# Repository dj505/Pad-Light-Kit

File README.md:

# Overkill PIU Pad Lighting Kit
An upgrade kit, if you consider a 5x5 RGB LED grid in the center of each panel to be an upgrade.  

# What is this?
I wanted to make a drop-in kit that replaced the original LEDs in Pump it Up dance pads with fancy StepManiaX-like RGB lighting. **This is only partially that.** Due to a variety of factors, it's not quite as drop-in as I'd hoped, but installation is still rather straightforward!

There are 2 PCB designs being worked on for this project:
* The main "Panel" PCB
    * Contains all the LEDs, with individual microcontrollers per PCB, ensuring they can all work individually.
    * Fully tested, with updated design/gerber files that hardware issues I initially ran into while prototyping.
* The power distrubution PCB
    * Takes a barrel jack and/or bare wires via screw terminals.
    * 5V input only! Make sure your power supply can pump out enough amps to power all the LEDs.
    * 5 outputs, one per arrow on one pad. In the case of DDR/ITG pads, one may be left unused.
    * Also includes footprints for filtering capacitors, which I haven't found to be necessary. Populate with 10uF 0805 capacitors if needed.

Unlike the PicoFX and my other previous hardware projects, this kit is not meant to be hand-soldered, although hand-solder friendly footprints were used where possible. As this likely will not be sold as a pre-made kit any time soon, be aware that it is not a beginner project. PCB manufacturing and assembly costs are rather affordable, but costs from part sourcing and shipping could add up.

# Compatibility & Overview

### This project is designed to be as easy as possible to install, but does require you to do some amount of manual part sourcing. Please pay close attention to power consumption and make sure you source parts that can support the kit.

This project is made for somewhat modern Pump it Up dance pads (FX through LX), but is plug-and-play compatible with:
* All Pump it Up dance pads **after** SD (SD pads used incandescent bulbs and will require some modification for use with this kit)
* In the Groove pads
* Older Dance Dance Revolution pads that use the same 2.54mm pitch connector (double check first!)
Please **pay close attention to the polarity** of the 12V connector printed on the PCB's silkscreen.  
The **yellow wire should go to 12V.** This may involve plugging the cable in upside down. That's okay. Just keep in mind the pins may need to be bent upwards slightly to accept the connector.

Without some modification to the pads and/or this kit, this project is untested or **NOT** plug-and-play compatible with:
* Pump it Up JUMP pads (unfortunate, I know)
* Modern Dance Dance Revolution pads
* Namco "Crapocab" DDR pads
* StepManiaX pads (for several reasons)
* Dance Master Super Station/3DDX
* EZ2Dancer
If the pads you want to use this project with have a **12V DC** wire that powers the original lights, whether it goes to existing LEDs or to an inverter, **this kit will function, but may require you to cut the wires and/or splice in a new connector.** It likely will also not fit the original mounting holes, in which case you'll need to tape it down or something.

Aside from the individual components required for each PCB, you will need:
* As many "Panel" PCBs as your upgrade requires
    * PIU pads require 5 per full pad, 10 in total for a complete setup
    * ITG/DDR pads require 4 per full pad, 8 in total for a complete setup
* A way to supply 5V with up to ~10A maximum current draw (50W or so)
    * This can be either one 5A power supply **per pad**, or one single super beefy power supply for **both pads simultaneously.**
    * If I did my math right, these metrics are based on the peak power comsumption when every single LED is lit up white at full brightness. **Only run your LEDs on full-brightness white for extended periods of time at your own risk; the kit was not developed with this use in mind.** (It would be bright as heck, though)
* Extra wiring to supply power to the new PCBs
    * I recommend 20AWG, anything thinner is not rated for the possible peak power consumption of one panel
* 2 pin male JST connectors (along with metal connector to be crimped to the wires)
    * These are listed here separately from the female connectors in the bill of materials, as you'll need quite a few.
    * 2 connectors are required per panel. One to connect to the lighting PCB, one to connect to the power distribution board.
* A crimping tool compatible with JST XH connectors (optional, but recommended)

# Main panel PCB
A full BOM can be generated using KiCad's schematic editor. Unlike my previous projects, such as the PicoFX or PicoIO, there are a *lot* of components that you will likely need to source yourself. Many of these have LCSC part numbers attached as an example, but are not guaranteed to be available through JLCPCB's assembly service.  
The following components (some of which are not required) are listed per **single** PCB:

### Bill of materials
|          Component          |              Reference              |          Footprint         |Quantity|
|-----------------------------|-------------------------------------|----------------------------|--------|
|100nF Capacitor              |C1, C2, C4, C5, C7-C9, C12, C14, C15 |SMD 0402                    |10      |
|1uF Capacitor                |C3, C6                               |SMD 0402                    |2       |
|27pF Capacitor               |C10, C11                             |SMD 0402                    |2       |
|10uF Capacitor               |C13, C16                             |SMD 0402                    |2       |
|WS2812B-V5 LED (!)           |D1-10, D12-26                        |PLCC4 5x5mm                 |25      |
|SS34 Diode                   |D27                                  |DO-214AC                    |1       |
|Green LED                    |D28                                  |SMD 0805                    |1       |
|nSMD025 Fuse                 |F1                                   |SMD 1206                    |1       |
|3 Pin Header \*              |J1                                   |2.54mm Pitch                |1       |
|USB Type C Port              |J2                                   |G-Switch GT-USB 7010ASV     |1       |
|2 Pin JST XH                 |J3                                   |2.50mm Pitch                |1       |
|2x6 Pin Header \*            |J4                                   |2.54mm Pitch                |1       |
|Molex 35312-0760 \~\~        |J5                                   |N/A                         |1       |
|Molex Mini-Fit Jr \~\~       |J6-J9                                |N/A                         |4       |
|2 Pin Header \~              |J10                                  |2.54mm Pitch, **Horizontal**|1       |
|3 Pin Header \*\*            |J11, J12                             |1.27mm Pitch, Not Required  |2       |
|1k Ohm Reistor               |R1, R8, R10                          |SMD 0402                    |3       |
|10k Ohm Resistor             |R2                                   |SMD 0402                    |1       |
|10K Ohm Resistor \*\*        |R3                                   |SMD 0402 (for SPI flash)    |1       |
|27 Ohm Resistor              |R4, R5                               |SMD 0402                    |2       |
|5.1k Ohm Resistor            |R6, R7                               |SMD 0402                    |2       |
|3k Ohm Resistor              |R9                                   |SMD 0402                    |1       |
|Tactile Button Switch        |SW1, SW2                             |6mm x 6mm                   |2       |
|W25Q32JVSS (or equivalent)   |U1                                   |SOIC-8                      |1       |
|Raspberry Pi RP2040          |U2                                   |QFN-56                      |1       |
|NCP1117 3.3V Output Regulator|U3                                   |SOT-223-3                   |1       |
|12.000MHz Crystal Oscillator |Y1                                   |HC49                        |1       |

(!) WS2812B-V5 LEDs don't require external capacitors, so there are no footprints for them on this board. Earlier revisions may not work properly without these capacitors.
\* Optional  
\*\* Do Not Fit (only required if a part malfunctions without it)  
\~ Required for old-style pads (FX and earlier)  
\~\~ Required for new-style pads (CX/TX and newer)  

All **SMD 0402** parts use hand-solder footprints in just in case, however if you do not own a reflow oven or hot air soldering station, please consider using an assembly service available through companies like PCBWay or JLCPCB for a better and more realiable end result. It does cost extra, but will be far less time consuming and far more reliable than soldering hundreds of components by hand.

# Power PCB
This part is extremely basic and just supplies power to the panels. Each PCB should be capable of supplying up to 8A, enough to power all 5 panels. Just make sure to hook it up to a power supply capable of delivering the necessary wattage.

### Bill of materials
|          Component          | Reference |          Footprint         |Quantity|
|-----------------------------|-----------|----------------------------|--------|
|10uF Capacitor \*            |C1-C5      |SMD 0805                    |5       |
|2 Pin Screw Terminal \*\*    |J1         |5mm Plugin Terminal         |1       |
|DC Barrel Jack \*\*          |J2         |2.5mm inner, 6.4mm Outer    |1       |
|2 Pin JST XH                 |J3-J7      |2.50mm Pitch                |5       |

\* Option/not strictly necessary. Serves a purpose, but shouldn't affect functionality if missing.  
\*\* Denotes parts that are interchangeable depending on how you want to power the board

This board lacks mounting holes and is intended to just be attached somewhere near the foot PCB or power supply with double sided tape. Placement is up to you. Footprints for a screw terminal and a DC jack are provided, depending on which is more suited to your use case. You could even solder the power wires straight to the PCB if you really want to.  

JST XH connectors with 20AWG wire will need to be routed from the power distrubution PCB to every individual panel PCB. This shouldn't be all that difficult, just a little extra time consuming. Having a crimping tool would make this far easier.

# Very Important Notes
**(Seriously, you're going to want to double check these!)**

### This kit will require dedicated external power, and there's no safe way around that!
This kit bumps the LED count up to 125 per pad. Stock pads have around 40 or fewer depending on pad model. Please don't try to power this off the cab's original 12V line! The original 22AWG wire is rated for roughly 0.92A. This kit can potentially draw up to 1A per panel, or 5A total per pad. Plus, the 12V line is used for signalling purposes with this kit, and it won't function correctly without it. **I've measured a draw of 0.874A for a single panel lit up white at full brightness, however this may not be consistent from build to build.** While 10A total is a worst-case scenario, be sure to stick to the following guidelines:  
* Make sure you use a power supply that's capable of supplying the necessary amount of power required by this kit, and pick a wire gauge capable of carrying the amount of power needed for each panel. I would recommend 20AWG.  
* You'll need a way to run power into the pads. If I can come up with a more elegant solution I'll be sure to post it in detail, but the holes present in the bottom corners of each arrow are safe bets as entry points for your wires.
* Even if you don't plan on running these at high enough power to draw 5A per pad (or the maximum you have measured on your own), don't skimp out on a power supply. Overdrawing the power supply will cause it to get uncomfortably warm (or worse), and will eventually destroy it. Spend the extra few bucks for safety!

### Make sure you use a bright solder mask!
White is recommended, green and others may also work, but black solder mask isn't known to be very reflective. It won't make a very big difference, but it will definitely look better and brighter.

### If you own a multimeter, check the voltage of the 12V line!
These boards get their "turn on and start animating" signal from the original 12V wiring that's meant to power the stock LEDs/inverters/what have you. To make this safe for the 3.3V RP2040 chip, a voltage divider is used. Until this design is eventually replaced with an optoisolator or other component, **you should do the following:**  
1. Unplug the stock LED
2. Hook up a voltmeter or a multimeter in DC mode to the connector
3. Ensure the connector supples **no less than 10V** and **no more than 13.2V** when supplying power  
If your measurement falls outside of this range and the power supply in your cab isn't adjustable, you may need to use different reistors for the voltage divider circuit.

If the connector is not supplying enough power, the microcontroller won't read it as a "high" signal to start animating the lights. If it's *too* high, you risk damaging the microcontroller. I've haven't seen any machines deviate from this general range before, so chances are you're fine, but make sure to double check. If your machine has a variable voltage power supply **and you know what you're doing**, you can adjust it slightly to fit within the safe range.

# Firmware Setup
This project runs on [CircuitPython for the Raspberry Pi Pico.](https://circuitpython.org/board/raspberry_pi_pico/). I'm not quite clever enough to create a special CircuitPython build specifically for this project yet, maybe one day!

1. Download the .uf2 file for CircuitPython. This project was developed using 7.3.3, but in between writing the firmware and actually receiving all the parts for a kit, 8.0.0 was released as a stable version, so the following instructions have been updated.
2. Plug the board into your PC. The BOOTSEL button shouldn't need to be held as the board should not yet be programmed. If for some reason it already is, use the BOOTSEL button.
3. The board should pop up as a USB mass storage device. Drag and drop the .uf2 file onto it. After a moment, it should disconnect, and you should see a "CIRCUITPY" drive appear in its place.
4. Open the "CIRCUITPY" drive, and copy the contents of this repository's "Firmware" directory onto it, overwriting code.py.
5. Download the [CircuitPython library bundle](https://circuitpython.org/libraries) that matches the version of CircuitPython you installed.
    * Look inside the "lib" directory for an "asyncio" folder. Copy this to the CIRCUITPY drive's "lib" folder.
    * Do the same for "adafruit_pixelbuf.mpy", "adafruit_ticks.mpy", and "neopixel.mpy".
6. Create your animations. See the instructions in /Firmware/README.md or use the included example animations.
    * Your animation should be a bitmap file titled "image.bmp" and located in the "bitmap" directory.
    * By default, there won't be a "bitmap" directory. You'll need to create this by hand or copy over the example one.
7. You're done! If everything is assembled and set up properly, your animations should now work, and the panel is ready to be installed.

# Installation
After assembling and setting up the firmware for each of the panels, actually installing them is the easy part. I'll update this section with photos when I have some.

1. Unplug and remove the original LEDs, and replace them with the new boards.
    * If the mounting holes *do* line up, use the original screws to secure the new boards in place.
    * If the mounting holes *don't* line up, double sided tape will do the trick!
    * You may have to remove some original parts to make room, depending on the pad. This mostly applies to much older pads that have fluorescent lights hooked up to inverters. Carefully remove these (they may be fragile!) and set them aside.
2. Find a power supply, and plan out where the wires are going to go.
    * I find the easiest way to do this is to hide the power supply underneath the dance pad and run the cable coming from the low voltage side in through the one of the 4 holes in the bottom of one of the arrow panels.
    * I would not recommend routing any AC wiring or power supply units inside of the dance pads for safety reasons. It's much safer to run the low voltage DC side in alone.
3. Mount the power distribution PCB.
    * Make sure it's within easy reach of the cable you'll be using to power it.
    * The placement here is entirely up to your discretion, just put it somewhere that allows you to easily run all the necessary wires. I mounted mine under the center panel.
    * This PCB has no mounting holes, since you'll be using double sided tape or other similar adhesive to mount it. Make sure any exposed contacts on the bottom are trimmed down and/or covered and so they do not make contact with the pad frame.
4. Run wires from the distribution board's outputs to each of your panels.
    * If you know what you're doing, and you thoroughly test the power consumption of your components, be sure to use a wire rated for the power draw. Otherwise, I recommend 20AWG wire. I personally measured a 0.874A peak power draw, but your build may differ.
    * You can either try to source wires with JST XH connectors on either end, or you can crimp these yourself.
    * If you crimp these yourself, buy a crimping tool! They don't cost a lot and they make things way way less of a pain. (They're still kind of a pain, though.)
    * Double check that the positive/negative connections line up on both sides of your wires.
5. Fire it up and give it a test!
    * If something doesn't work, move onto the troubleshooting section.

# Jumper Options
These jumpers are currently unused. Please feel free to reach out and suggest features!

# Bypassing the Voltage Divider
There's a small set of jumper pads underneath and to the right of the connector for the 12V light header header that is meant to bypass the voltage divider. This is meant to allow the panel to be easily used in home pads or DIY pads using an Arduino-like main board. **Do not bridge this jumper if using anything higher than a 3.3V to control the lights.**

To use this feature, you must:
* Make sure you remove resistors R9 and R10 underneath the header if they are currently installed. Otherwise, exclude these components during the initial asssembly.
* Make sure the GPIO you're going to connect this to operates at a **3.3 volt logic level!** The RP2040 is **not 5V tolerant** and applying 5V to the GPIO can cause irreversible damage.

If you plan to use a 5V microcontroller, you must **not** bridge the jumper, and should instead adjust the values of the resistors in the voltage divider accordingly.

# Troubleshooting
This list will be expanded as potential issues crop up.
* **No lights or pattern on the LED grid**
    1. Make sure the bitmap is in the "bitmap" directory, and is named "bitmap.bmp".
    2. Check that external power is connected. A USB connection will not power the LEDs.
    3. Re-export your bitmap through GIMP with the correct settings:
        * 24-bit colour depth
        * Run-length encoding **disabled**
        * Saving colour space information doesn't seem to make a difference, but if in doubt, disable it
* **Pattern displays, but doesn't look right**
    1. Make sure your spritesheet is made up of exactly 5x5 pixel sprites, all of which should be stacked vertically. More than one column will not work.
    2. Re-export your bitmap through GIMP with the correct settings. See step 3 under "No lights or pattern on the LED grid."
* **All the LEDs past a certain point fail to light up**
    1. Check the solder points on and around the LED where the chain is broken.
        * The strip goes from left to right on the first row, then right to left on the second row, zigzagging back and forth.
        * If any single LED is not properly connected, it can either light up but not send a signal to the next one, or fail to light up itself.
        * Carefully re-solder any bad connections and test again.
    2. Ensure the LEDs are oriented correctly.
        * With the USB port on the top left corner, the notch on every LED should be on the bottom right side.
        * Any LEDs that aren't oriented properly will need to be desoldered and rotated.
* **One single LED doesn't light up, but the rest work**
    1. Add some flux to each leg of the LED and reflow the solder.
        * Screwing the PCB down into the pad may slightly bend it, causing a poor connection on one or more LEDs.
        * Reflowing the solder usually fixes this fault. Current revisions of the PCB with slightly larger mounting holes should be less susceptible to it.

# Credits
Thanks to:
- [sugoku](https://github.com/sugoku) for the Molex 35312 series footprints

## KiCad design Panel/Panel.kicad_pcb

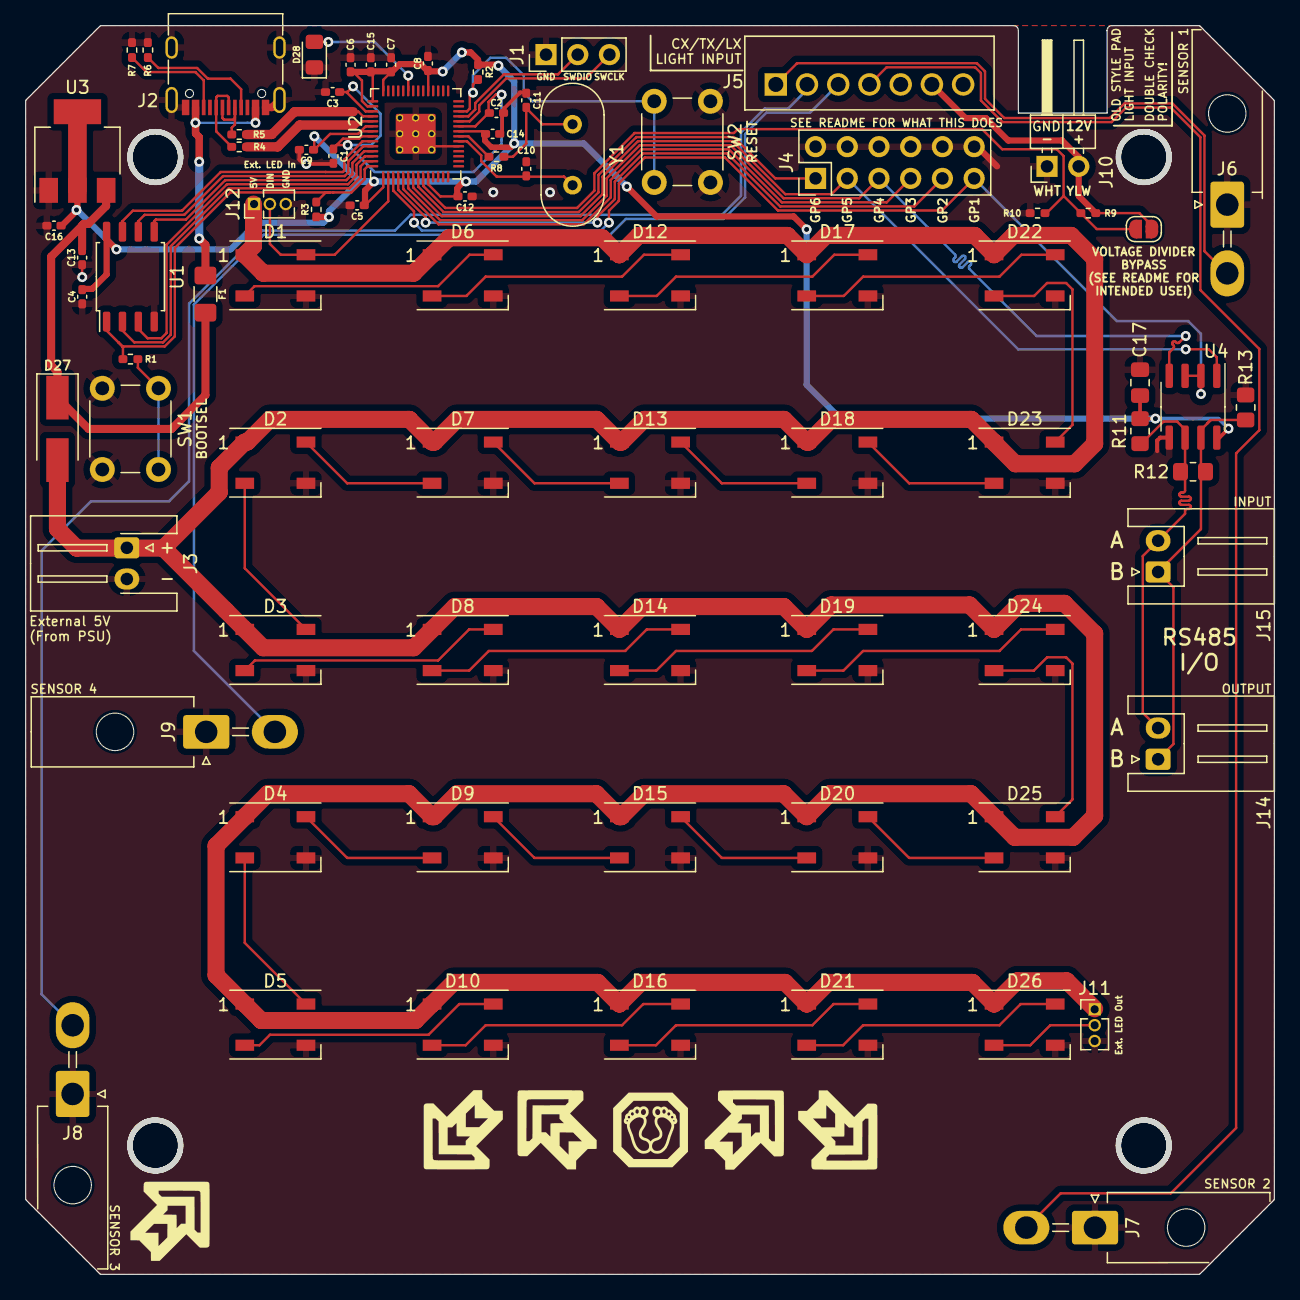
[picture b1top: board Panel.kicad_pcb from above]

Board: 2 copper layers, 100.0 x 100.0 mm, 80 parts (0 on the bottom side), 66 nets.

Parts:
C1, C2, C4, C5, C7, C8, C9, C12, C14, C15: 100nF; C_0402_1005Metric_Pad0.74x0.62mm_HandSolder
C3, C6: 1uF; C_0402_1005Metric_Pad0.74x0.62mm_HandSolder
C10, C11: 27pF; C_0402_1005Metric_Pad0.74x0.62mm_HandSolder
C13, C16: 10uF; C_0402_1005Metric_Pad0.74x0.62mm_HandSolder
C17: 100nF; C_0805_2012Metric_Pad1.18x1.45mm_HandSolder
D1, D2, D3, D4, D5, D6, D7, D8, D9, D10, D12, D13, D14, D15, D16, D17, D18, D19, D20, D21, D22, D23, D24, D25, D26: WS2812B; LED_WS2812B_PLCC4_5.0x5.0mm_P3.2mm
D27: SS34; D_SMA_Handsoldering
D28: LED_Small; LED_0805_2012Metric_Pad1.15x1.40mm_HandSolder
F1: 500mA; Fuse_1206_3216Metric_Pad1.42x1.75mm_HandSolder
J1: Conn_01x03; PinHeader_1x03_P2.54mm_Vertical
J2: USB_C_Receptacle_USB2.0; USB_C_Receptacle_G-Switch_GT-USB-7010ASV
J3: Conn_01x02; JST_XH_S2B-XH-A-1_1x02_P2.50mm_Horizontal
J4: Conn_02x06_Odd_Even; PinHeader_2x06_P2.54mm_Vertical
J5: Conn_01x07; 35312-0760
J6, J7, J8, J9: Conn_01x02; Molex_Mini-Fit_Jr_5569-02A2_2x01_P4.20mm_Horizontal
J10: Conn_01x02; PinHeader_1x02_P2.54mm_Horizontal
J11, J12: Conn_01x03; PinHeader_1x03_P1.27mm_Vertical
J14, J15: Conn_01x02; JST_XH_S2B-XH-A_1x02_P2.50mm_Horizontal
JP1: Jumper_2_Open; SolderJumper-2_P1.3mm_Open_RoundedPad1.0x1.5mm
R1, R8, R10: 1k; R_0402_1005Metric_Pad0.72x0.64mm_HandSolder
R2: 10k; R_0402_1005Metric_Pad0.72x0.64mm_HandSolder
R3: DNF; R_0402_1005Metric_Pad0.72x0.64mm_HandSolder
R4, R5: 27 Ohm; R_0402_1005Metric_Pad0.72x0.64mm_HandSolder
R6, R7: 5.1k; R_0402_1005Metric_Pad0.72x0.64mm_HandSolder
R9: 3k; R_0402_1005Metric_Pad0.72x0.64mm_HandSolder
R11, R13: 4.7k; R_0805_2012Metric_Pad1.20x1.40mm_HandSolder
R12: 120; R_0805_2012Metric_Pad1.20x1.40mm_HandSolder
SW1, SW2: SW_Push; SW_PUSH_6mm
U1: W25Q32JVSS; SOIC-8_5.23x5.23mm_P1.27mm
U2: RP2040; RP2040-QFN-56
U3: NCP1117-3.3_SOT223; SOT-223-3_TabPin2
U4: SP3485EN; SOIC-8_3.9x4.9mm_P1.27mm
Y1: 12.000MHz; Crystal_HC49-4H_Vertical

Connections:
+1V1: C1.1, C2.1, C3.1, U2.23 (DVDD), U2.45 (VREG_VOUT), U2.50 (DVDD)
+3V3: C4.1, C5.1, C6.1, C7.1, C8.1, C9.1, C12.1, C14.1, C15.1, C16.1, C17.1, R2.1, R3.1, R11.1, U1.8 (VCC), U2.1 (IOVDD), U2.10 (IOVDD), U2.22 (IOVDD), U2.33 (IOVDD), U2.42 (IOVDD), U2.43 (ADC_AVDD), U2.44 (VREG_IN), U2.48 (USB_VDD), U2.49 (IOVDD), U3.2 (VO), U4.8 (VCC)
+5V: C13.1, D27.1 (K), F1.2, U3.3 (VI)
/RS485_A: J14.2, J15.2, R11.2, R12.1, U4.6 (A)
/RS485_B: J14.1, J15.1, R12.2, R13.1, U4.7 (B)
Ext 5V: D1.1 (VDD), D2.1 (VDD), D3.1 (VDD), D4.1 (VDD), D5.1 (VDD), D6.1 (VDD), D7.1 (VDD), D8.1 (VDD), D9.1 (VDD), D10.1 (VDD), D12.1 (VDD), D13.1 (VDD), D14.1 (VDD), D15.1 (VDD), D16.1 (VDD), D17.1 (VDD), D18.1 (VDD), D19.1 (VDD), D20.1 (VDD), D21.1 (VDD), D22.1 (VDD), D23.1 (VDD), D24.1 (VDD), D25.1 (VDD), D26.1 (VDD), D27.2 (A), J3.1, J11.1, J12.1
GND: C1.2, C2.2, C3.2, C4.2, C5.2, C6.2, C7.2, C8.2, C9.2, C10.1, C11.1, C12.2, C13.2, C14.2, C15.2, C16.2, C17.2, D1.3 (VSS), D2.3 (VSS), D3.3 (VSS), D4.3 (VSS), D5.3 (VSS), D6.3 (VSS), D7.3 (VSS), D8.3 (VSS), D9.3 (VSS), D10.3 (VSS), D12.3 (VSS), D13.3 (VSS), D14.3 (VSS), D15.3 (VSS), D16.3 (VSS), D17.3 (VSS), D18.3 (VSS), D19.3 (VSS), D20.3 (VSS), D21.3 (VSS), D22.3 (VSS), D23.3 (VSS), D24.3 (VSS), D25.3 (VSS), D26.3 (VSS), D28.1 (K), J1.1, J2.A1 (GND), J2.A12 (GND), J2.B1 (GND), J2.B12 (GND), J2.S1 (SHIELD), J3.2, J4.2, J4.4, J4.6, J4.8, J4.10, J4.12, J5.7, J6.1, J7.1, J8.1, J9.1, J10.1, J11.3, J12.3, R6.2, R7.1, R10.2, R13.2, SW1.1, SW2.2, U1.4 (GND), U2.19 (TESTEN), U2.57 (GND), U3.1 (GND), U4.5 (GND)
GPIO0: D1.4 (DIN), J12.2, U2.2 (GPIO0)
GPIO1: J4.11, U2.3 (GPIO1), U4.2 (~RE), U4.3 (DE)
GPIO2: J4.9, U2.4 (GPIO2)
GPIO3: J4.7, U2.5 (GPIO3)
GPIO4: J4.5, U2.6 (GPIO4), U4.4 (DI)
GPIO5: J4.3, U2.7 (GPIO5), U4.1 (RO)
GPIO6: J4.1, U2.8 (GPIO6)
GPIO7: JP1.1 (A), R9.2, R10.1, U2.9 (GPIO7)
LIGHT EN: J5.6, J10.2, JP1.2 (B), R9.1
unnamed: C11.2, R8.1, Y1.1
unnamed: D1.2 (DOUT), D6.4 (DIN)
unnamed: D2.4 (DIN), D7.2 (DOUT)
unnamed: D2.2 (DOUT), D3.4 (DIN)
unnamed: D3.2 (DOUT), D8.4 (DIN)
unnamed: D4.4 (DIN), D9.2 (DOUT)
unnamed: D4.2 (DOUT), D5.4 (DIN)
unnamed: D5.2 (DOUT), D10.4 (DIN)
unnamed: D10.2 (DOUT), D16.4 (DIN)
unnamed: D6.2 (DOUT), D12.4 (DIN)
unnamed: D12.2 (DOUT), D17.4 (DIN)
unnamed: D13.4 (DIN), D18.2 (DOUT)
unnamed: D7.4 (DIN), D13.2 (DOUT)
unnamed: D8.2 (DOUT), D14.4 (DIN)
unnamed: D14.2 (DOUT), D19.4 (DIN)
unnamed: D15.4 (DIN), D20.2 (DOUT)
unnamed: D9.4 (DIN), D15.2 (DOUT)
unnamed: D16.2 (DOUT), D21.4 (DIN)
unnamed: D17.2 (DOUT), D22.4 (DIN)
unnamed: D18.4 (DIN), D23.2 (DOUT)
unnamed: D19.2 (DOUT), D24.4 (DIN)
unnamed: D20.4 (DIN), D25.2 (DOUT)
unnamed: D21.2 (DOUT), D26.4 (DIN)
unnamed: D22.2 (DOUT), D23.4 (DIN)
unnamed: D24.2 (DOUT), D25.4 (DIN)
unnamed: D26.2 (DOUT), J11.2
unnamed: D28.2 (A), U2.37 (GPIO25)
unnamed: F1.1, J2.A4 (VBUS), J2.A9 (VBUS), J2.B4 (VBUS), J2.B9 (VBUS)
unnamed: J2.A5 (CC1), R6.1
unnamed: J2.B5 (CC2), R7.2
unnamed: R1.1, SW1.2
unnamed: R5.1, U2.46 (USB_DM)
unnamed: R4.1, U2.47 (USB_DP)
QSPI_SCLK: U1.6 (CLK), U2.52 (QSPI_SCLK)
QSPI_SD0: U1.5 (DI(IO0)), U2.53 (QSPI_SD0)
QSPI_SD1: U1.2 (DO(IO1)), U2.55 (QSPI_SD1)
QSPI_SD2: U1.3 (IO2), U2.54 (QSPI_SD2)
QSPI_SD3: U1.7 (IO3), U2.51 (QSPI_SD3)
QSPI_SS: R1.2, R3.2, U1.1 (~CS), U2.56 (QSPI_SS)
RUN: R2.2, SW2.1, U2.26 (RUN)
SENSOR 1: J5.1, J6.2
SENSOR 2: J5.4, J7.2
SENSOR 3: J5.2, J8.2
SENSOR 4: J5.3, J9.2
SWCLK: J1.3, U2.24 (SWCLK)
SWDIO: J1.2, U2.25 (SWD)
USB D+: J2.A6 (D+), J2.B6 (D+), R4.2
USB D-: J2.A7 (D-), J2.B7 (D-), R5.2
XIN: C10.2, U2.20 (XIN), Y1.2
XOUT: R8.2, U2.21 (XOUT)

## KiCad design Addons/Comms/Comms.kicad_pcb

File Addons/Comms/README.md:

# Comms
This addon is made for **panel PCB rev. 2 and earlier**. Revision 3 has this functionality built-in and it is no longer necessary.

The "Comms" addon is meant to allow each panel to communicate robustly using RS485 through SP3485 chips to synchronize lighting patterns and other settings.

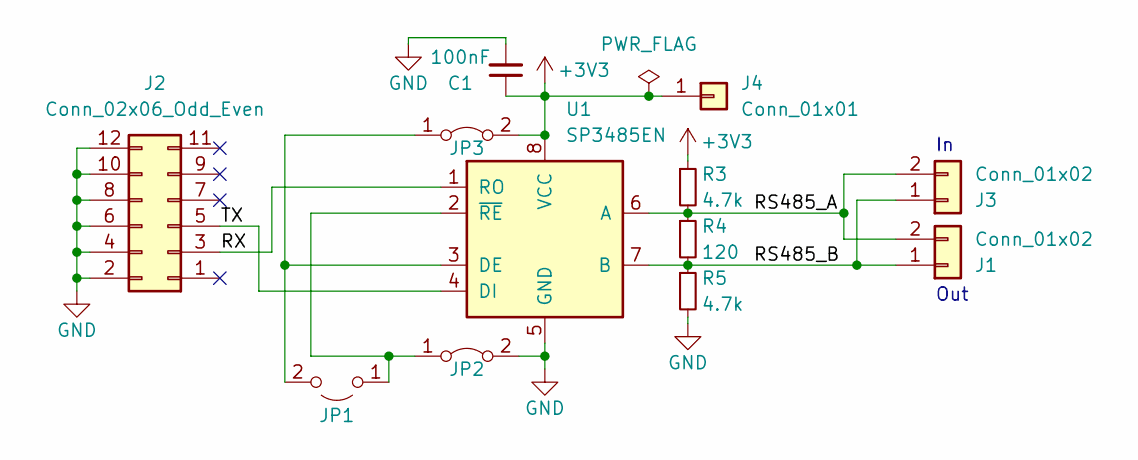
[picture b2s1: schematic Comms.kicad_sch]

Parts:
C1: 100nF; C_0805_2012Metric_Pad1.18x1.45mm_HandSolder; LCSC C49678
J1, J3: Conn_01x02; JST_XH_S2B-XH-A_1x02_P2.50mm_Horizontal
J2: Conn_02x06_Odd_Even; PinHeader_2x06_P2.54mm_Vertical
J4: Conn_01x01; PinHeader_1x01_P2.54mm_Vertical
JP1: Jumper_2_Open; SolderJumper-2_P1.3mm_Open_RoundedPad1.0x1.5mm
JP2, JP3: Jumper_2_Bridged; SolderJumper-2_P1.3mm_Bridged_RoundedPad1.0x1.5mm
R3, R5: 4.7k; R_0805_2012Metric_Pad1.20x1.40mm_HandSolder; LCSC C17673
R4: 120; R_0805_2012Metric_Pad1.20x1.40mm_HandSolder; LCSC C17437
U1: SP3485EN; SOIC-8_3.9x4.9mm_P1.27mm; LCSC C8963

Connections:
+3V3: C1.1, J4.1, JP3.2 (B), R3.1, U1.8 (VCC)
/RS485_A: J1.2, J3.2, R3.2, R4.1, U1.6 (A)
/RS485_B: J1.1, J3.1, R4.2, R5.1, U1.7 (B)
/RX: J2.3, U1.1 (RO)
/TX: J2.5, U1.4 (DI)
GND: C1.2, J2.2, J2.4, J2.6, J2.8, J2.10, J2.12, JP2.2 (B), R5.2, U1.5 (GND)
unnamed: JP1.1 (A), JP2.1 (A), U1.2 (~RE)
unnamed: JP1.2 (B), JP3.1 (A), U1.3 (DE)

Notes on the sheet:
Out

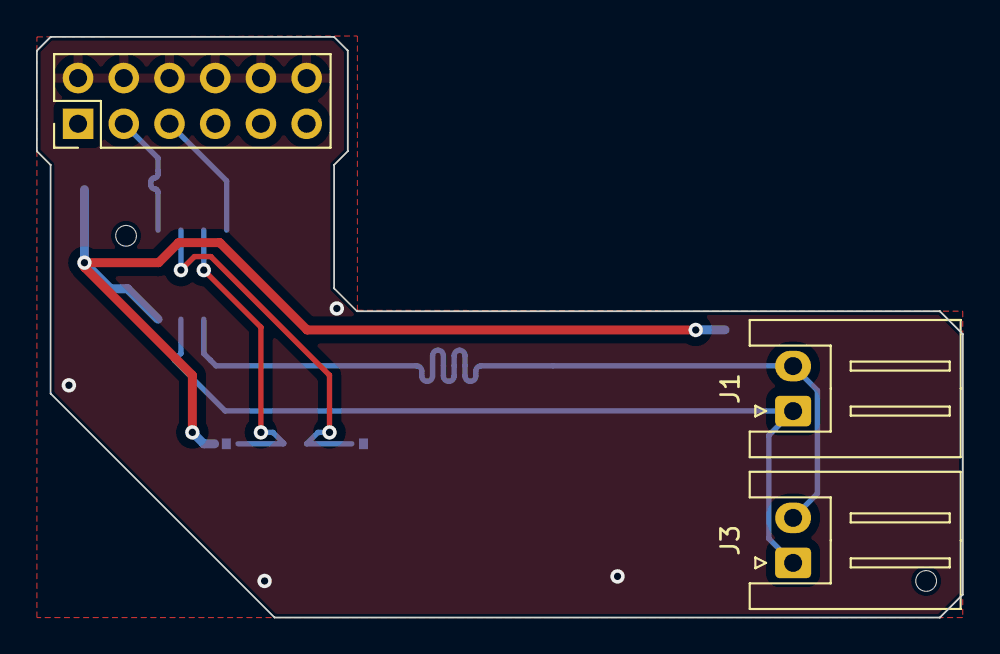
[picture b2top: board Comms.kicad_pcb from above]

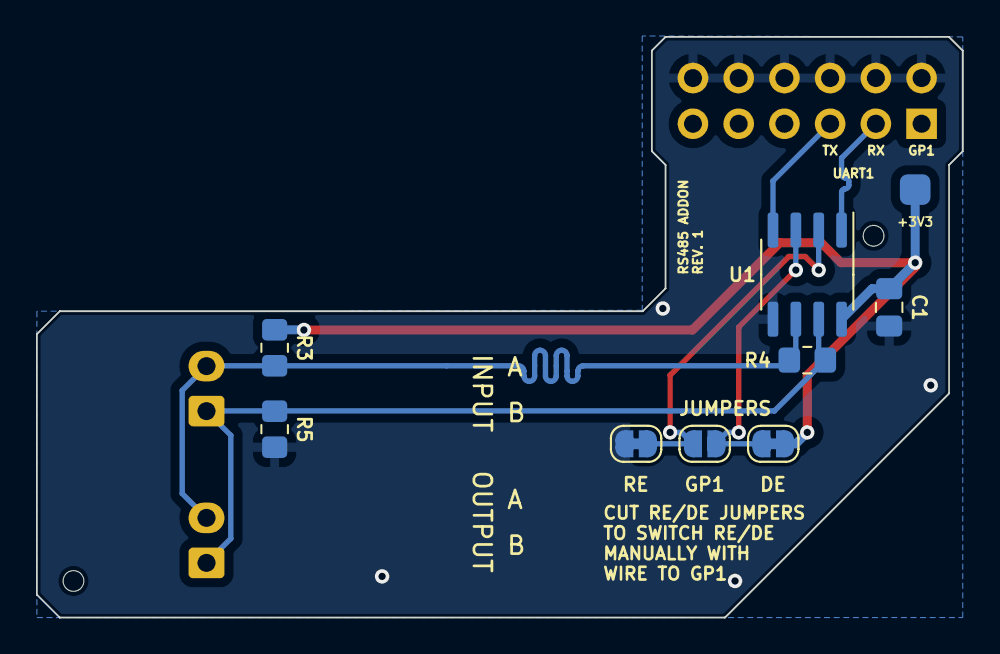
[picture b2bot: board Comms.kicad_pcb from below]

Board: 2 copper layers, 51.4 x 32.3 mm, 12 parts (9 on the bottom side), 8 nets.

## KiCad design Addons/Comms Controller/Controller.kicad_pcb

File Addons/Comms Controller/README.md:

# Comms Controller
This addon is meant for **all current revisions** of the Pad Light Kit main board. As of writing, the current revision is **Rev. 3.**

This addon allows patterns to be uploaded to the main board(s) over RS485. Don't mix up the RS485 and power connectors!

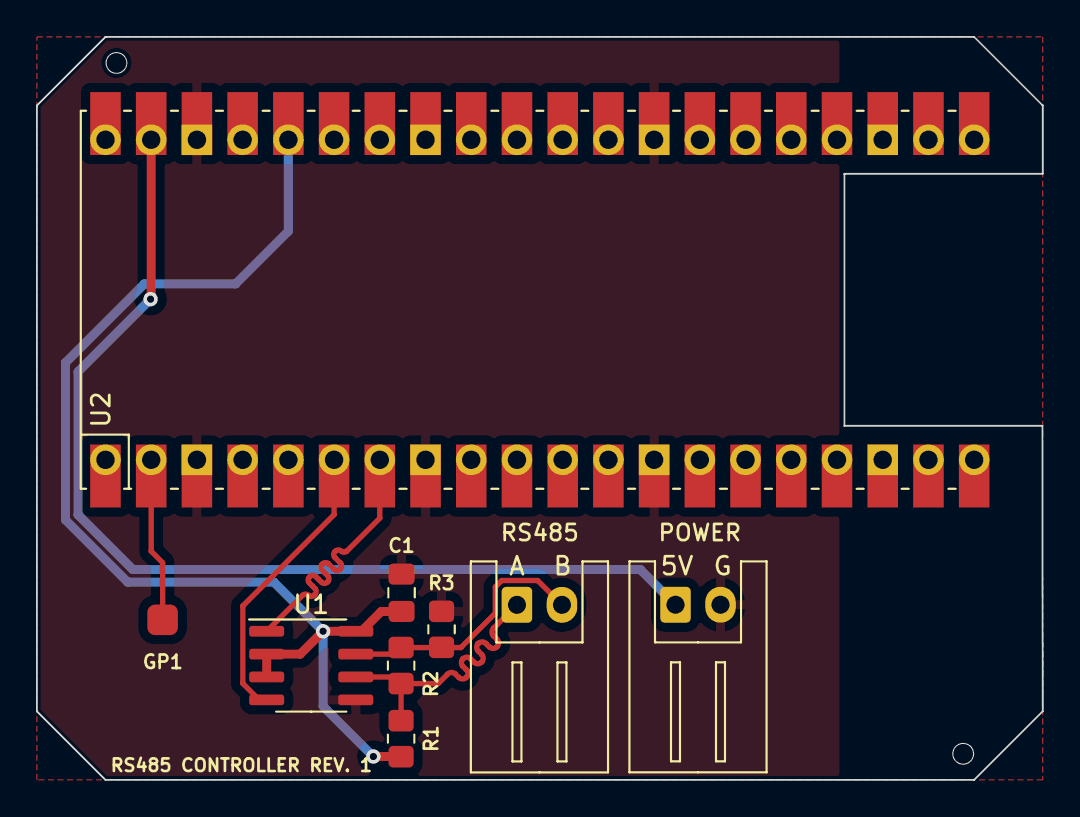
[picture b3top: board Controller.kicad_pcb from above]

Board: 2 copper layers, 55.9 x 41.3 mm, 9 parts (0 on the bottom side), 8 nets.

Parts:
C1: 100nF; C_0805_2012Metric_Pad1.18x1.45mm_HandSolder
J1: GP1 Bodge; PinSocket_1x01_P2.54mm_Vertical
J2, J3: Conn_01x02; JST_XH_S2B-XH-A_1x02_P2.50mm_Horizontal
R1, R3: 4.7k; R_0805_2012Metric_Pad1.20x1.40mm_HandSolder
R2: 120; R_0805_2012Metric_Pad1.20x1.40mm_HandSolder
U1: SP3485EN; SOIC-8_3.9x4.9mm_P1.27mm
U2: Pico; RPi_Pico_SMD_TH

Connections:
+3V3: C1.1, R1.1, U1.2 (~RE), U1.3 (DE), U1.8 (VCC), U2.36 (3V3)
+5V: J3.1, U2.39 (VSYS)
/RS485_A: J2.1, R1.2, R2.1, U1.6 (A)
/RS485_B: J2.2, R2.2, R3.1, U1.7 (B)
GND: C1.2, J3.2, R3.2, U1.5 (GND), U2.3 (GND), U2.8 (GND), U2.13 (GND), U2.18 (GND), U2.23 (GND), U2.28 (GND), U2.38 (GND)
unnamed: J1.1, U2.2 (GPIO1)
RX: U1.1 (RO), U2.7 (GPIO5)
TX: U1.4 (DI), U2.6 (GPIO4)

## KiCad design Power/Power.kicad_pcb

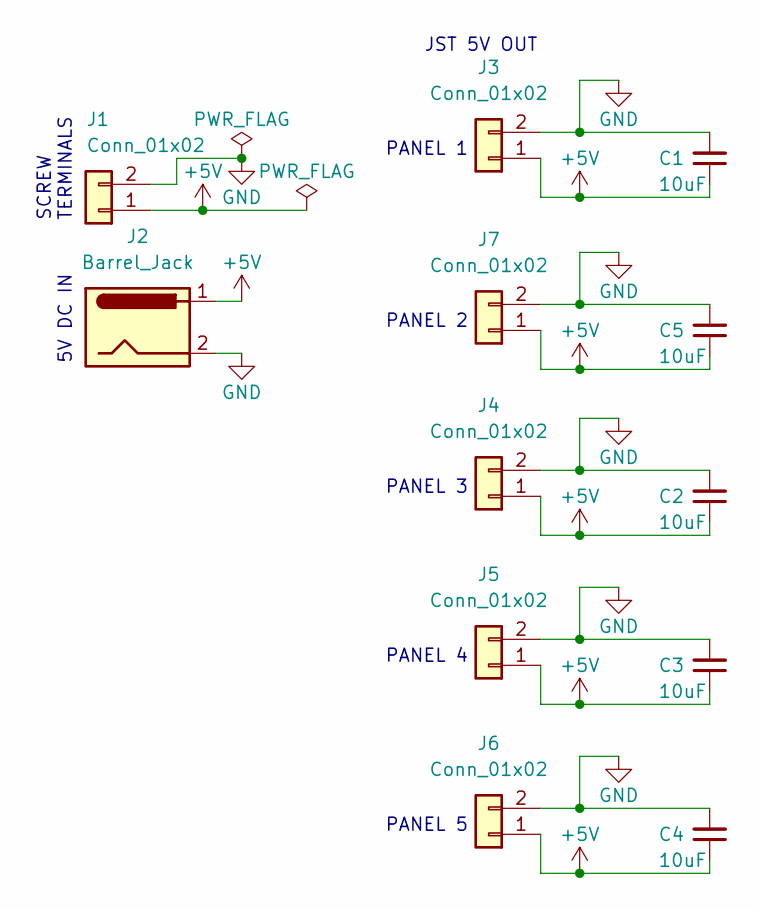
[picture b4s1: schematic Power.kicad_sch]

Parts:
C1, C2, C3, C4, C5: 10uF; C_0805_2012Metric_Pad1.18x1.45mm_HandSolder
J1: Conn_01x02; TerminalBlock_bornier-2_P5.08mm
J2: Barrel_Jack; BarrelJack_CUI_PJ-063AH_Horizontal
J3, J4, J5, J6, J7: Conn_01x02; JST_XH_B2B-XH-A_1x02_P2.50mm_Vertical

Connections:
+5V: C1.1, C2.1, C3.1, C4.1, C5.1, J1.1, J2.1, J3.1, J4.1, J5.1, J6.1, J7.1
GND: C1.2, C2.2, C3.2, C4.2, C5.2, J1.2, J2.2, J2.MP, J3.2, J4.2, J5.2, J6.2, J7.2

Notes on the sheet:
PANEL 4
JST 5V OUT
SCREW TERMINALS
PANEL 2
PANEL 1
5V DC IN
PANEL 3
PANEL 5

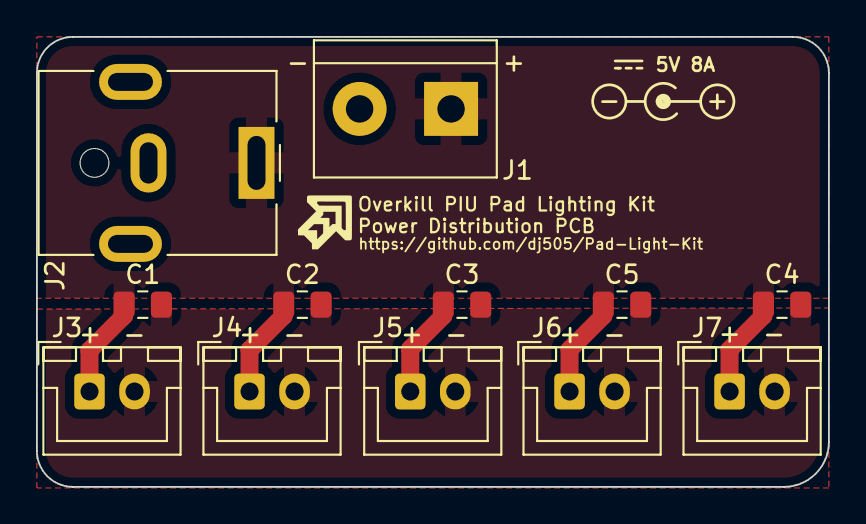
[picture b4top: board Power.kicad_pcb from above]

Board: 2 copper layers, 44.0 x 25.0 mm, 12 parts (0 on the bottom side), 2 nets.

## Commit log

2023-01-18 Initial schematics (Mainly RP2040)
2023-01-18 Initial component placement
2023-01-19 90% routed
2023-01-19 Complete panel PCB
2023-01-20 Final Panel changes + first prod run gerber
2023-01-20 Add credits to readme (oops)
2023-01-20 Add more labels to PCB silkscreen, update README
2023-01-20 README formatting fixes
2023-01-20 Initial power distribution PCB design
2023-01-24 Update power distribution PCB
2023-01-24 Power distribution PCB final rev. + gerber
2023-01-25 Begin work on firmware, update README
2023-01-25 Add example bitmaps, update readmes
2023-01-26 Padded bitmap decoding + animation
2023-01-26 Fix mirrored even rows, other misc things
2023-01-27 Add power PCB info
2023-01-27 Fix critical issue - KiCad assigned LED pins wrong
    This would result in any boards manufactured with this design being unusable without cutting traces and bodging connections.
2023-01-27 Tidy up routing
2023-01-27 Fix hole alignment, tidy more routing
2023-01-27 Minor changes
2023-01-27 Hopefully final nitpicks and adjustments
2023-01-27 Fix major schematic issue and parity warnings
2023-01-27 Final touches (hopefully for real this time)
2023-01-31 Add output polarity labels to silkscreen
2023-01-31 Update power board gerbers
2023-02-07 New example bitmaps, update code, update readme
2023-02-09 Add USB protection, GP25 LED, silkscreen tweaks
2023-02-10 Fix pin assignments
2023-02-13 Enlarge mounting holes slightly
2023-02-13 Minor silkscreen touchups
2023-02-15 Update readme, add rainbow animations, minor tweaks
2023-02-15 both of these values were wrong lol
2023-02-15 Update to KiCAD 7, add ref designators to README
2023-06-14 Initial comms board design
2023-06-14 don't bridge 3v3 and ground lol
2023-08-03 Add RS485 functionality & addons, several fixes
2023-08-03 Add voltage divider bypass for home pad use
2023-08-03 Fix an oopsie, control RE/DE via GPIO by default
2024-07-20 Replaced USB C port with cheaper alternative
2024-07-20 Fixed an unconnected track that was actually connected but still tripped DRC
